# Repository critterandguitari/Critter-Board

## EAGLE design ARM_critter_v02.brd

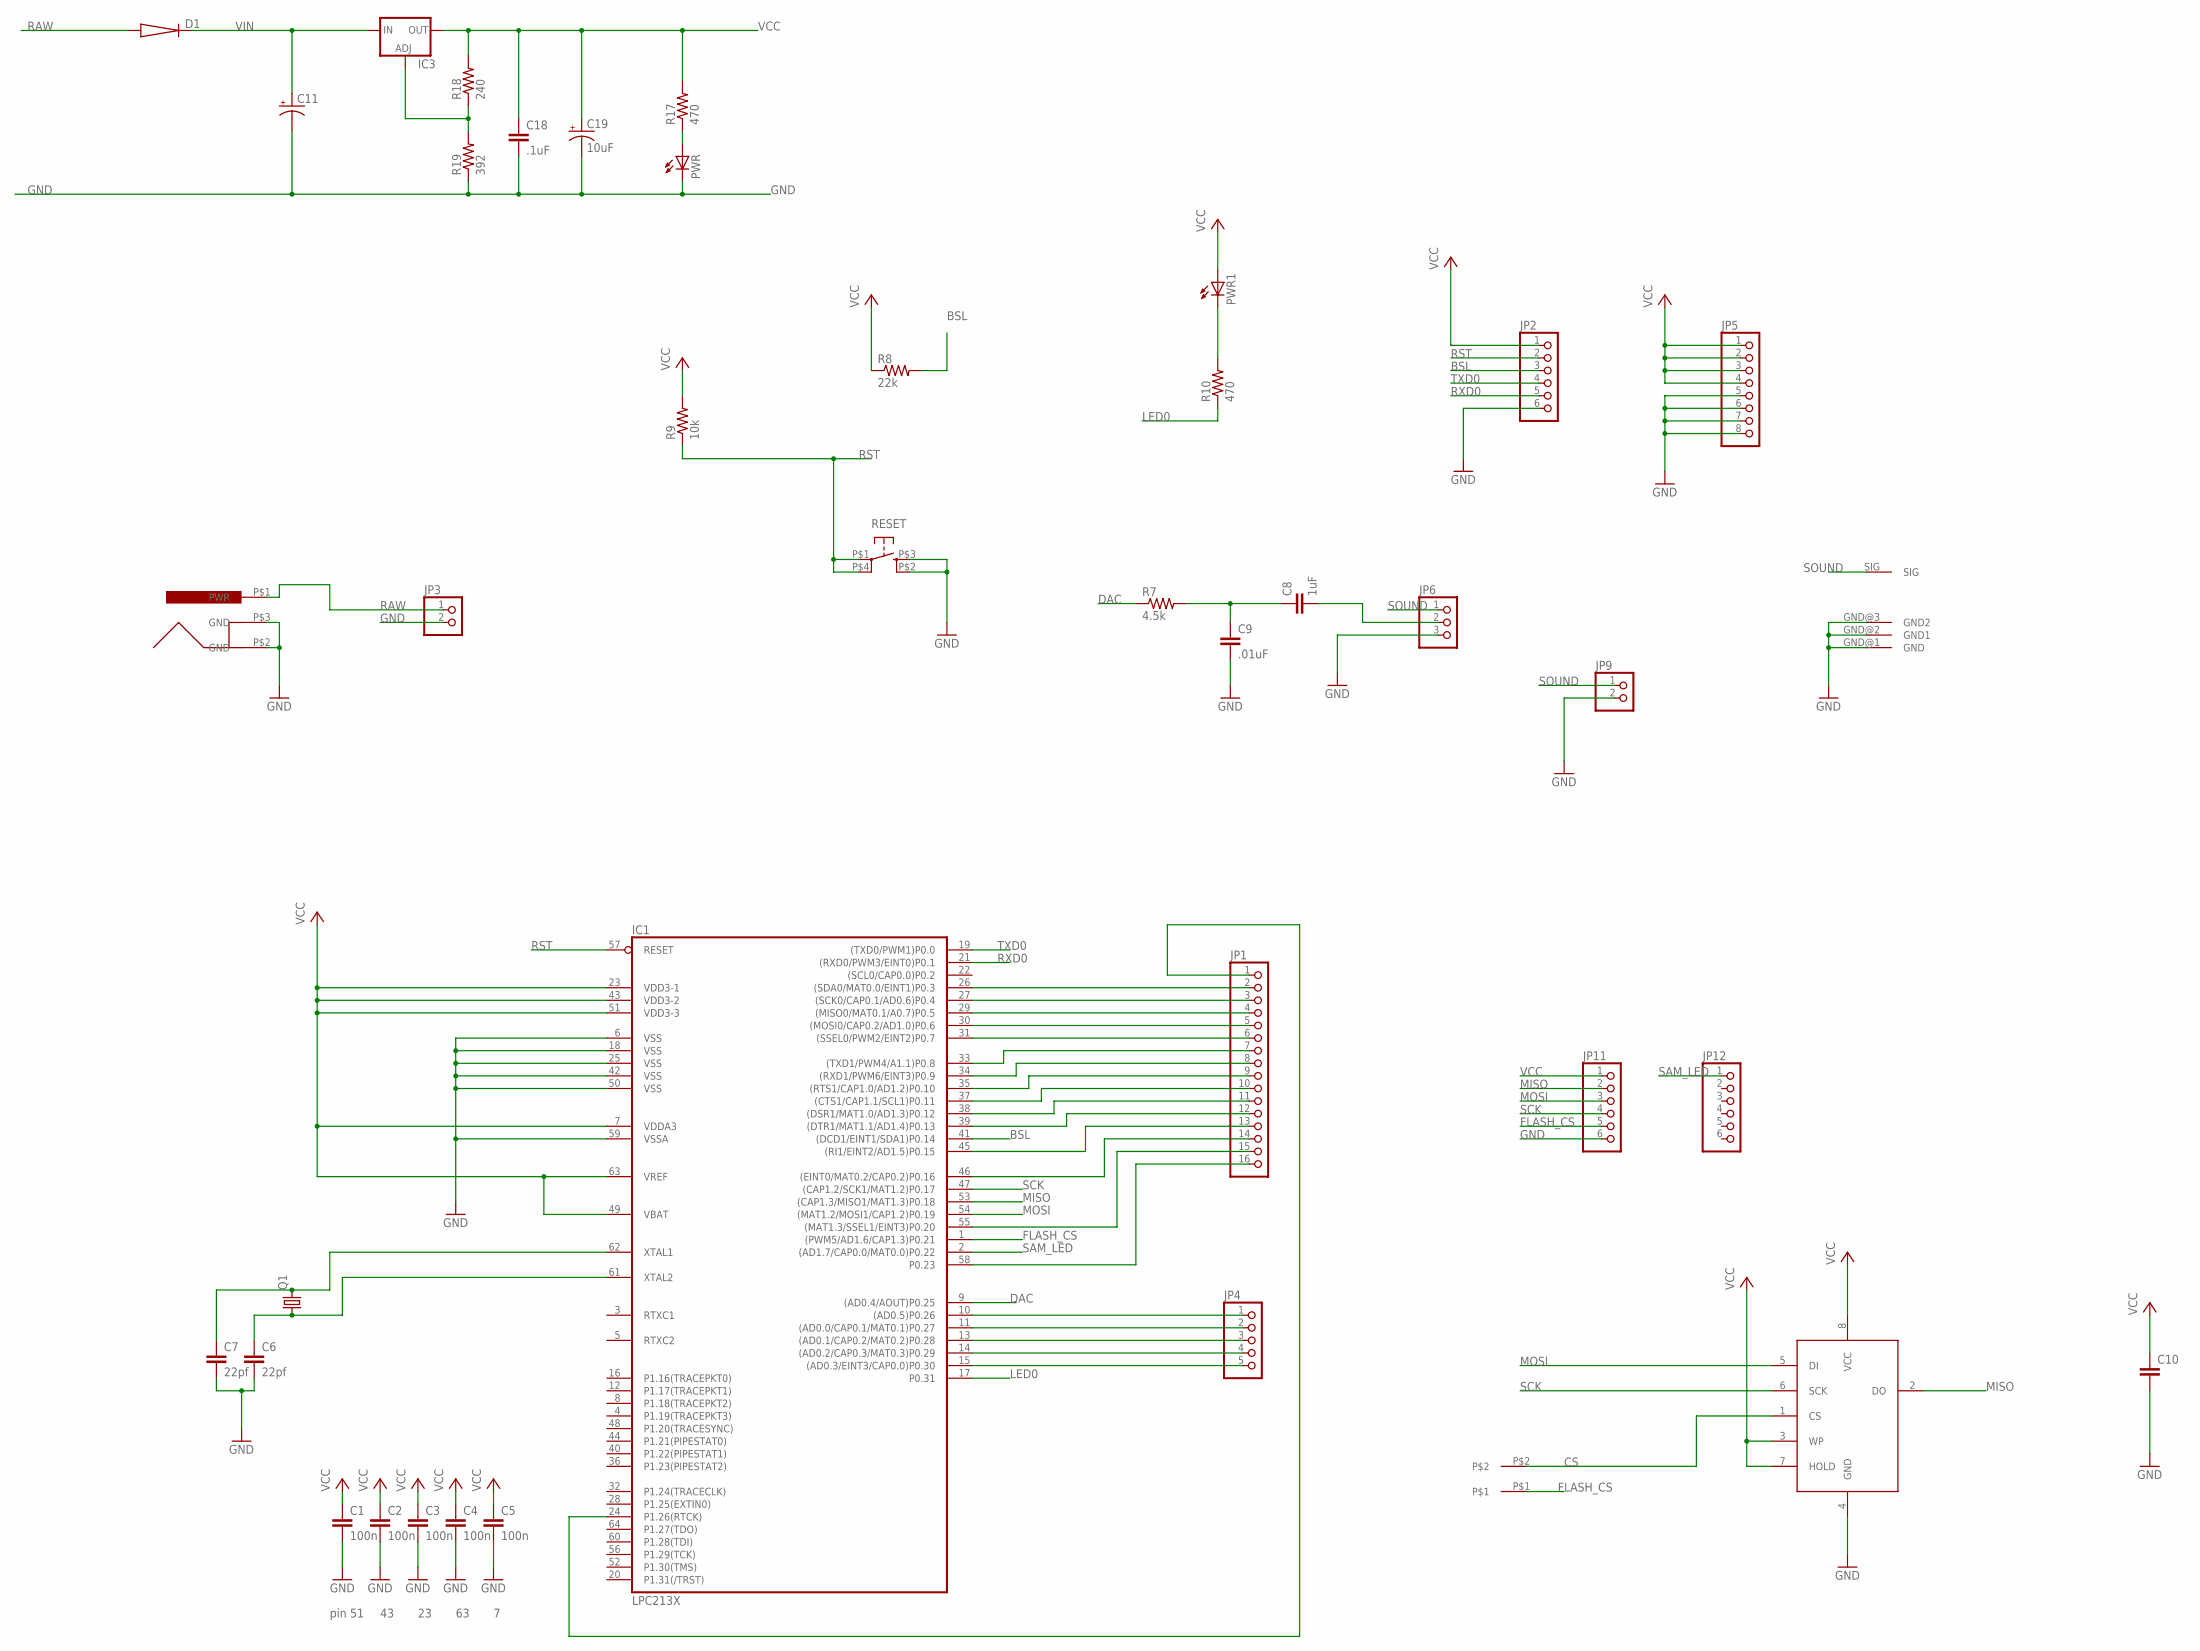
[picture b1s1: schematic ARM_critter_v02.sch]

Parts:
C1, C2, C3, C4, C5: 100n; C0603
C6, C7: 22pf; C0603
C8: 1uF; C0603
C9: .01uF; C0603
C10: CAP0603; C0603
C11: CPOL-USE3.5-8; E3,5-8
C18: .1uF; C0603
C19: 10uF; CPOL_1206
D1: DIODESMB; SMB
IC1: LPC213X; SQFP-S-10X10-64
IC3: V_REG_FAN1117SOT223; SOT223
JP1: PINHD-1X16; 1X16
JP2, JP11, JP12: PINHD-1X6; 1X06
JP3, JP9: PINHD-1X2; 1X02
JP4: PINHD-1X5; 1X05
JP5: PINHD-1X8; 1X08
JP6: PINHD-1X3; 1X03
PWR, PWR1: LED1206; CHIPLED_1206
Q1: CRYSTALHC49UV; HC49U-V
R7: 4.5k; R0603
R8: 22k; R0603
R9: 10k; R0603
R10, R17: 470; R0603
R18: 240; R0603
R19: 392; R0603
RESET: RESET_SWITCH; TACTILE_SWITCH_SMD
U$1: POWER_JACK
U$2: M25PXX; SO08
U$3: JUMPER_SOL
U$5: PHONO_PLUG; PHONO_PCB

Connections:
BSL: IC1.41 ((DCD1/EINT1/SDA1)P0.14), JP2.3, R8.2
CS: U$2.1 (CS), U$3.P$2
DAC: IC1.9 ((AD0.4/AOUT)P0.25), R7.1
FLASH_CS: IC1.1 ((PWM5/AD1.6/CAP1.3)P0.21), JP11.5, U$3.P$1
GND: C1.2, C2.2, C3.2, C4.2, C5.2, C6.2, C7.2, C9.2, C10.2, C11.-, C18.2, C19.C (-), IC1.6 (VSS), IC1.18 (VSS), IC1.25 (VSS), IC1.42 (VSS), IC1.50 (VSS), IC1.59 (VSSA), JP2.6, JP3.2, JP5.5, JP5.6, JP5.7, JP5.8, JP6.3, JP9.2, JP11.6, PWR.C, R19.1, RESET.P$2 (S1), RESET.P$3 (S), U$1.P$2 (GND), U$1.P$3 (GND), U$2.4 (GND), U$5.GND@1 (GND), U$5.GND@2 (GND1), U$5.GND@3 (GND2)
LED0: IC1.17 (P0.31), R10.1
MISO: IC1.53 ((CAP1.3/MISO1/MAT1.3)P0.18), JP11.2, U$2.2 (DO)
MOSI: IC1.54 ((MAT1.2/MOSI1/CAP1.2)P0.19), JP11.3, U$2.5 (DI)
unnamed: C8.1, C9.1, R7.2
unnamed: C7.1, IC1.62 (XTAL1), Q1.2
unnamed: C6.1, IC1.61 (XTAL2), Q1.1
unnamed: PWR1.C, R10.2
unnamed: IC1.24 (P1.26(RTCK)), JP1.1
unnamed: C8.2, JP6.2
unnamed: IC1.26 ((SDA0/MAT0.0/EINT1)P0.3), JP1.2
unnamed: IC1.27 ((SCK0/CAP0.1/AD0.6)P0.4), JP1.3
unnamed: IC3.1 (ADJ), R18.1, R19.2
unnamed: IC1.29 ((MISO0/MAT0.1/A0.7)P0.5), JP1.4
unnamed: IC1.30 ((MOSI0/CAP0.2/AD1.0)P0.6), JP1.5
unnamed: IC1.31 ((SSEL0/PWM2/EINT2)P0.7), JP1.6
unnamed: IC1.33 ((TXD1/PWM4/A1.1)P0.8), JP1.7
unnamed: IC1.34 ((RXD1/PWM6/EINT3)P0.9), JP1.8
unnamed: IC1.35 ((RTS1/CAP1.0/AD1.2)P0.10), JP1.9
unnamed: IC1.37 ((CTS1/CAP1.1/SCL1)P0.11), JP1.10
unnamed: IC1.38 ((DSR1/MAT1.0/AD1.3)P0.12), JP1.11
unnamed: IC1.39 ((DTR1/MAT1.1/AD1.4)P0.13), JP1.12
unnamed: IC1.45 ((RI1/EINT2/AD1.5)P0.15), JP1.13
unnamed: IC1.46 ((EINT0/MAT0.2/CAP0.2)P0.16), JP1.14
unnamed: IC1.55 ((MAT1.3/SSEL1/EINT3)P0.20), JP1.15
unnamed: PWR.A, R17.1
unnamed: IC1.58 (P0.23), JP1.16
unnamed: IC1.10 ((AD0.5)P0.26), JP4.1
unnamed: IC1.11 ((AD0.0/CAP0.1/MAT0.1)P0.27), JP4.2
unnamed: IC1.13 ((AD0.1/CAP0.2/MAT0.2)P0.28), JP4.3
unnamed: IC1.14 ((AD0.2/CAP0.3/MAT0.3)P0.29), JP4.4
unnamed: IC1.15 ((AD0.3/EINT3/CAP0.0)P0.30), JP4.5
RAW: D1.2 (C), JP3.1, U$1.P$1 (PWR)
RST: IC1.57 (RESET), JP2.2, R9.1, RESET.P$1, RESET.P$4 (P1)
RXD0: IC1.21 ((RXD0/PWM3/EINT0)P0.1), JP2.5
SAM_LED: IC1.2 ((AD1.7/CAP0.0/MAT0.0)P0.22), JP12.1
SCK: IC1.47 ((CAP1.2/SCK1/MAT1.2)P0.17), JP11.4, U$2.6 (SCK)
SOUND: JP6.1, JP9.1, U$5.SIG
TXD0: IC1.19 ((TXD0/PWM1)P0.0), JP2.4
VCC: C1.1, C2.1, C3.1, C4.1, C5.1, C10.1, C18.1, C19.A (+), IC1.7 (VDDA3), IC1.23 (VDD3-1), IC1.43 (VDD3-2), IC1.49 (VBAT), IC1.51 (VDD3-3), IC1.63 (VREF), IC3.2 (OUT), JP2.1, JP5.1, JP5.2, JP5.3, JP5.4, JP11.1, PWR1.A, R8.1, R9.2, R17.2, R18.2, U$2.3 (WP), U$2.7 (HOLD), U$2.8 (VCC)
VIN: C11.+, D1.1 (A), IC3.3 (IN)

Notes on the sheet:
pin 51

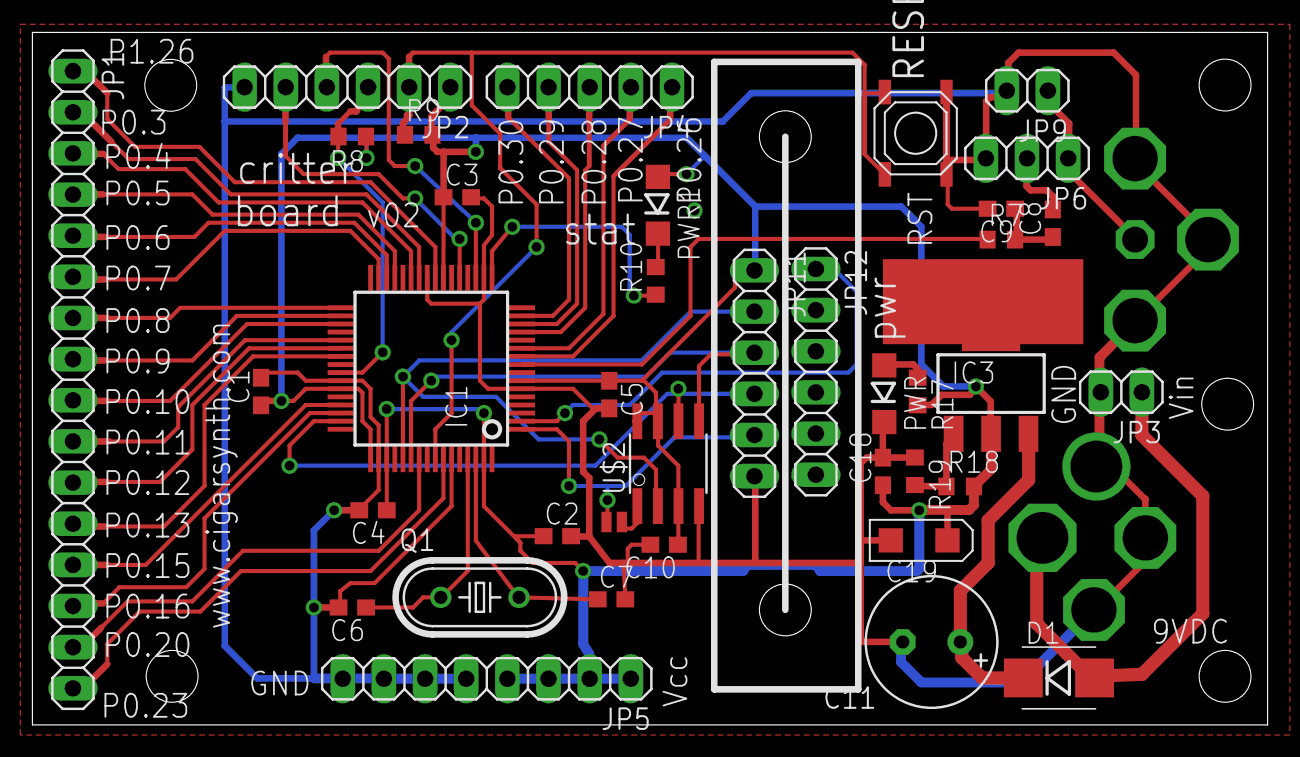
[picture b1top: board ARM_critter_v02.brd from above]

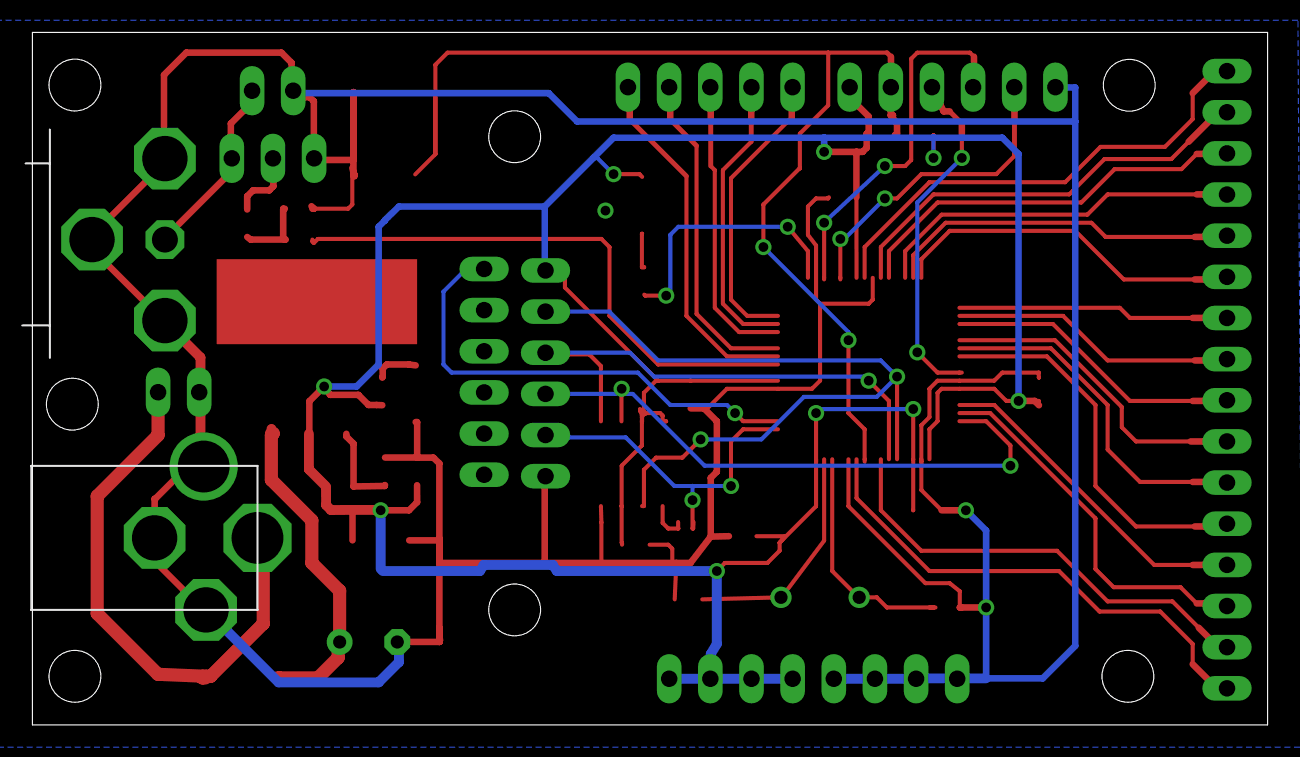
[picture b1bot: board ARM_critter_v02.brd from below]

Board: 2 copper layers, 76.2 x 42.8 mm, 40 parts (2 on the bottom side), 45 nets.

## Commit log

2013-04-21 adding eagle files
